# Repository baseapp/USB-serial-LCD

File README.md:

BaseApp USB-serial LCD/Keypad
-----------------------------

Supports HD44780 compatible LCDs(in 4-bit mode). Enumerates as a serial com port, and can be
used with software like LCD smartie for windows, or LCDproc etc. for
linux using matrixorbital commands. Also supports upto 4x4 matrix keypad.

List of supported matrix orbital commands supported is in MatrixOrbital.h

Code is based on http://dangerousprototypes.com/docs/USB_Universal_LCD_backpack

- This code is for PIC18F25K50, and can me modified easily for 18f45k50,
  both do not require external crystal for USB.
- No bootloader
- Keypad press/release output on serial

- Compiler - tested with mplabc18 v3.44
- Requires USB stack from microchip applications library

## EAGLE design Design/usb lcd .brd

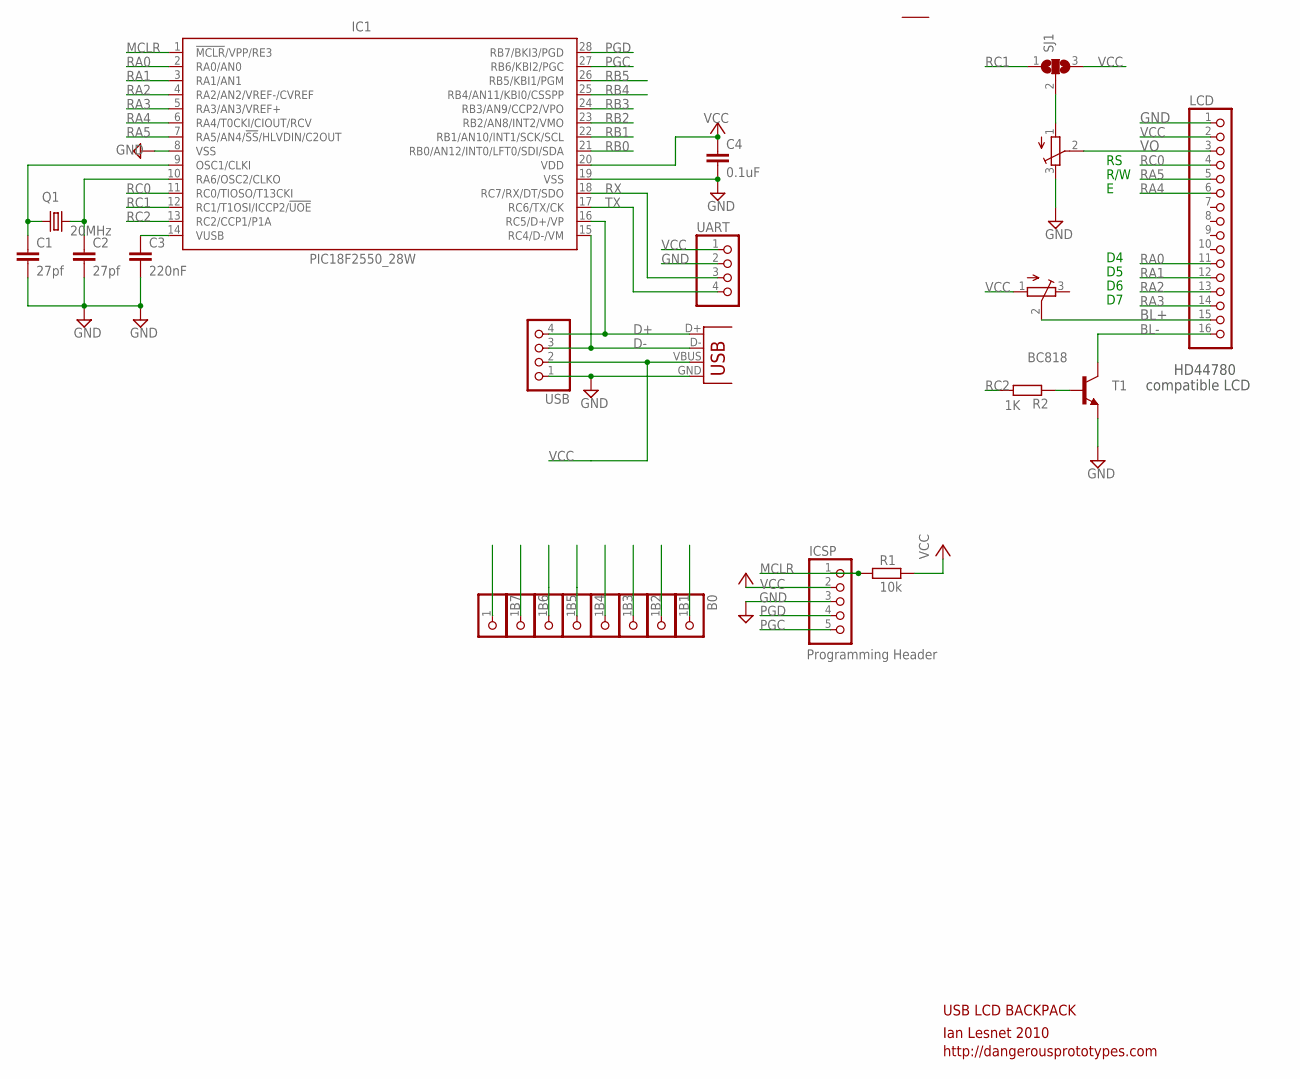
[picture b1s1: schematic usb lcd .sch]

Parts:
B0, B1, B2, B3, B4, B5, B6, B7: PINHD-1X1; 1X01
C1, C2: 27pf; C0805
C3: 220nF; C0805
C4: 0.1uF; C0805
IC1: PIC18F2550_28W; SO28W
ICSP: PINHD-1X5; 1X05
J1: USBSMD; USB-MINIB
LCD: PINHD-1X16; 1X16
Q1: 20MHz; HC49UP
R1: 10k; R0805
R2: 1K; M0805
SJ1: SJ2W; SJ_2
T1: BC818; SOT23-BEC
U$3, U$4: 3MM_TRIMPOT
UART: PINHD-1X4; 1X04
USB: PINHD-1X4; 1X04

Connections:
BASE: R2.1, T1.B
BL+: LCD.15, U$4.2 (S)
BL-: LCD.16, T1.C
D+: IC1.16 (RC5/D+/VP), J1.D+, USB.4
D-: IC1.15 (RC4/D-/VM), J1.D-, USB.3
GND: C1.2, C2.2, C3.2, C4.2, IC1.8 (VSS), IC1.19 (VSS), ICSP.3, J1.GND, LCD.1, T1.E, U$3.3 (E), UART.2, USB.1
MCLR: IC1.1 (!MCLR!/VPP/RE3), ICSP.1, R1.1
unnamed: SJ1.2, U$3.1 (A)
unnamed: C2.1, IC1.10 (RA6/OSC2/CLKO), Q1.2
unnamed: C1.1, IC1.9 (OSC1/CLKI), Q1.1
unnamed: C3.1, IC1.14 (VUSB)
PGC: B6.1, IC1.27 (RB6/KBI2/PGC), ICSP.5
PGD: B7.1, IC1.28 (RB7/BKI3/PGD), ICSP.4
RA0: IC1.2 (RA0/AN0), LCD.11
RA1: IC1.3 (RA1/AN1), LCD.12
RA2: IC1.4 (RA2/AN2/VREF-/CVREF), LCD.13
RA3: IC1.5 (RA3/AN3/VREF+), LCD.14
RA4: IC1.6 (RA4/T0CKI/CIOUT/RCV), LCD.6
RA5: IC1.7 (RA5/AN4/!SS!/HLVDIN/C2OUT), LCD.5
RB0: B0.1, IC1.21 (RB0/AN12/INT0/LFT0/SDI/SDA)
RB1: B1.1, IC1.22 (RB1/AN10/INT1/SCK/SCL)
RB2: B2.1, IC1.23 (RB2/AN8/INT2/VMO)
RB3: B3.1, IC1.24 (RB3/AN9/CCP2/VPO)
RB4: B4.1, IC1.25 (RB4/AN11/KBI0/CSSPP)
RB5: B5.1, IC1.26 (RB5/KBI1/PGM)
RC0: IC1.11 (RC0/TIOSO/T13CKI), LCD.4
RC1: IC1.12 (RC1/T1OSI/ICCP2/!UOE), SJ1.1
RC2: IC1.13 (RC2/CCP1/P1A), R2.2
RX: IC1.18 (RC7/RX/DT/SDO), UART.3
TX: IC1.17 (RC6/TX/CK), UART.4
VCC: C4.1, IC1.20 (VDD), ICSP.2, J1.VBUS, LCD.2, R1.2, SJ1.3, U$4.1 (A), UART.1, USB.2
VO: LCD.3, U$3.2 (S)

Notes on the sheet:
USB LCD BACKPACK
Ian Lesnet 2010
http://dangerousprototypes.com
HD44780
compatible LCD
R/W
Programming Header

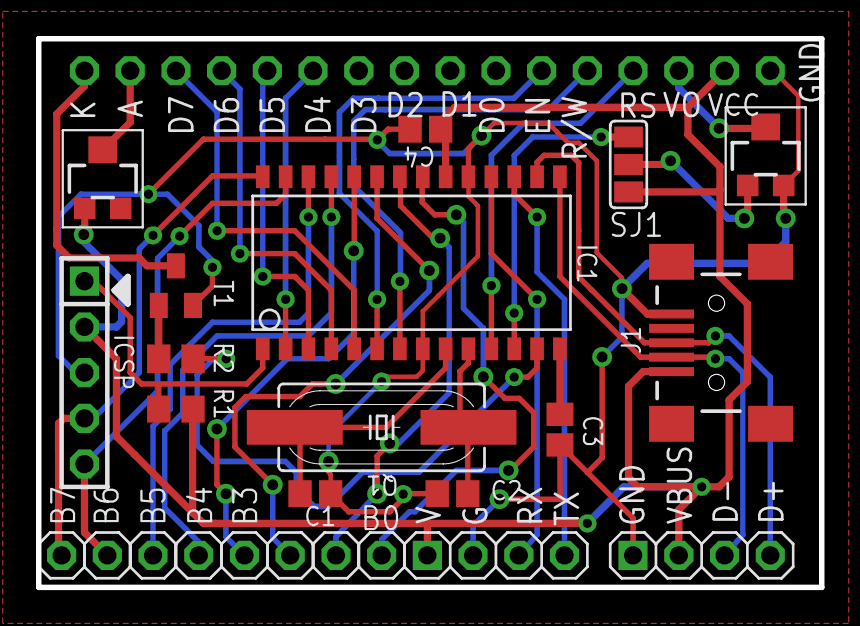
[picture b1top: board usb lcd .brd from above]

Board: 2 copper layers, 43.5 x 30.5 mm, 25 parts (1 on the bottom side), 32 nets.

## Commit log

2013-01-19 Note about 4-bit mode
2013-01-28 Added support for backlight brightness and contrast control commands.
2013-01-28 Moved code to firmarware dir.
2013-01-28 Added design files.
2013-01-28 mv README.md

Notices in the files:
Design/usb lcd .brd:
CC-BY-SA
